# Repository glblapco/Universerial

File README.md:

# Universerial

USB to UART bridge meant to be used on Hardware Hacking.

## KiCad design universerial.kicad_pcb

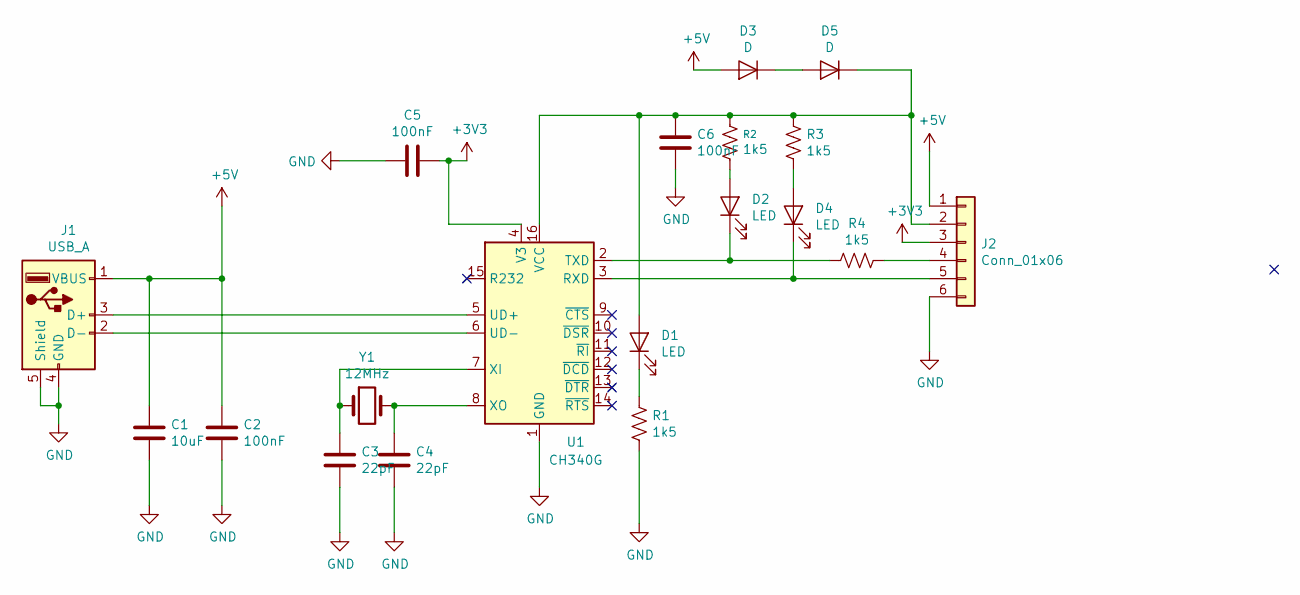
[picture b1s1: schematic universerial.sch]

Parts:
C1: 10uF; C_0201_0603Metric
C2, C5, C6: 100nF; C_0201_0603Metric
C3, C4: 22pF; C_0201_0603Metric
D1, D2, D4: LED; LED-L1T2_LUMILEDS
D3, D5: D; D_0201_0603Metric
J1: USB_A; USB_A_CNCTech_1001-011-01101_Horizontal
J2: Conn_01x06; Harwin_M20-89006xx_1x06_P2.54mm_Horizontal
R1, R2, R3, R4: 1k5; R_0201_0603Metric
U1: CH340G; SOIC-16_3.9x9.9mm_P1.27mm
Y1: 12MHz; Crystal_AT310_D3.0mm_L10.0mm_Horizontal

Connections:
+3V3: C5.1, J2.3, U1.4 (V3)
+5V: C1.1, C2.1, D3.2 (A), J1.1 (VBUS), J2.1
GND: C1.2, C2.2, C3.2, C4.2, C5.2, C6.2, J1.4 (GND), J1.5 (Shield), J2.6, R1.1, U1.1 (GND)
unnamed: C3.1, U1.7 (XI), Y1.1
unnamed: C4.1, U1.8 (XO), Y1.2
unnamed: C6.1, D1.2 (A), D5.1 (K), J2.2, R2.1, R3.1, U1.16 (VCC)
unnamed: D1.1 (K), R1.2
unnamed: D2.1 (K), R4.2, U1.2 (TXD)
unnamed: D2.2 (A), R2.2
unnamed: D3.1 (K), D5.2 (A)
unnamed: D4.1 (K), J2.5, U1.3 (RXD)
unnamed: D4.2 (A), R3.2
unnamed: J1.2 (D-), U1.6 (UD-)
unnamed: J1.3 (D+), U1.5 (UD+)
unnamed: J2.4, R4.1

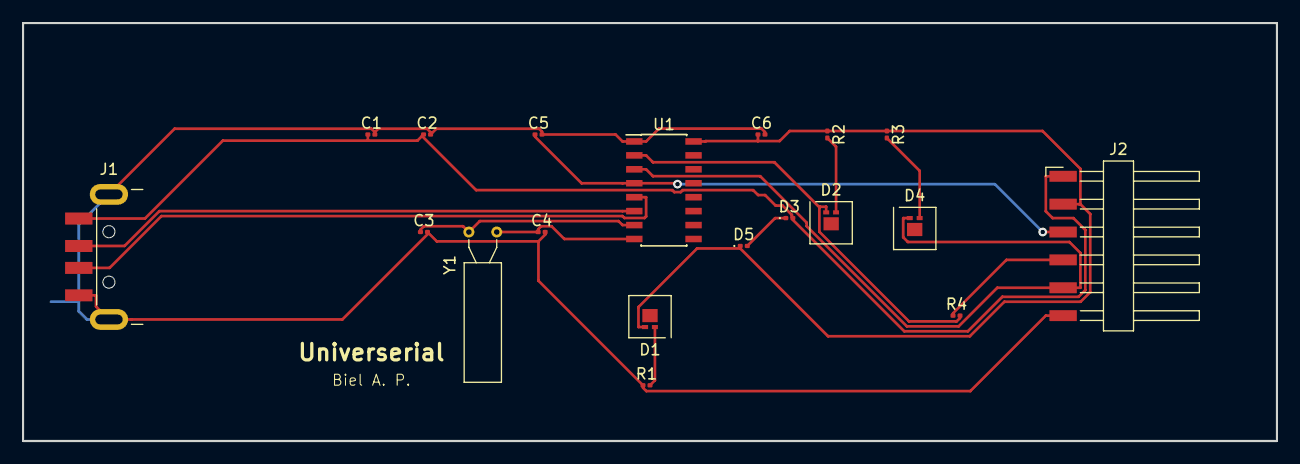
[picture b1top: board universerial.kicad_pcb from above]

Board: 2 copper layers, 114.3 x 38.1 mm, 19 parts (0 on the bottom side), 15 nets.

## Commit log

2021-08-05 Start.
2021-08-05 Finish USB connections.
2021-08-05 Connect VCC and 3.3V.
2021-08-05 Connect RXD, TXD and chip's GND.
2021-08-05 Connect chip's XI and XO.
2021-08-05 Leave useless pins disconnected.
2021-08-05 Fix VCC placement.
2021-08-05 Finish schematic.
2021-08-05 Annotate schematic.
2021-08-05 Assign footprints.
2021-08-05 Add netlist.
2021-08-05 Add BOM.
2021-08-05 Start PCB design.
2021-08-05 Organize PCB.
2021-08-05 Finish PCB.
2021-08-05 README.md
2021-08-05 Add drills and gerbers.
2021-08-12 update stuff.
2021-08-12 README
